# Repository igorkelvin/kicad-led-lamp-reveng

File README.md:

# LED Lamp Rev. Engineering

## Description

Made on KiCad using manual measurements without consulting official schematics for study purposes.

You may find the pdf version of the  in *./extra* folder.

Used a *Pelicano LED* from LLUM for reference, you can check it [at this catalog][catalog].

[catalog]: http://www.bronzearte.com.br/marketing/catalogo.pdf#page=59

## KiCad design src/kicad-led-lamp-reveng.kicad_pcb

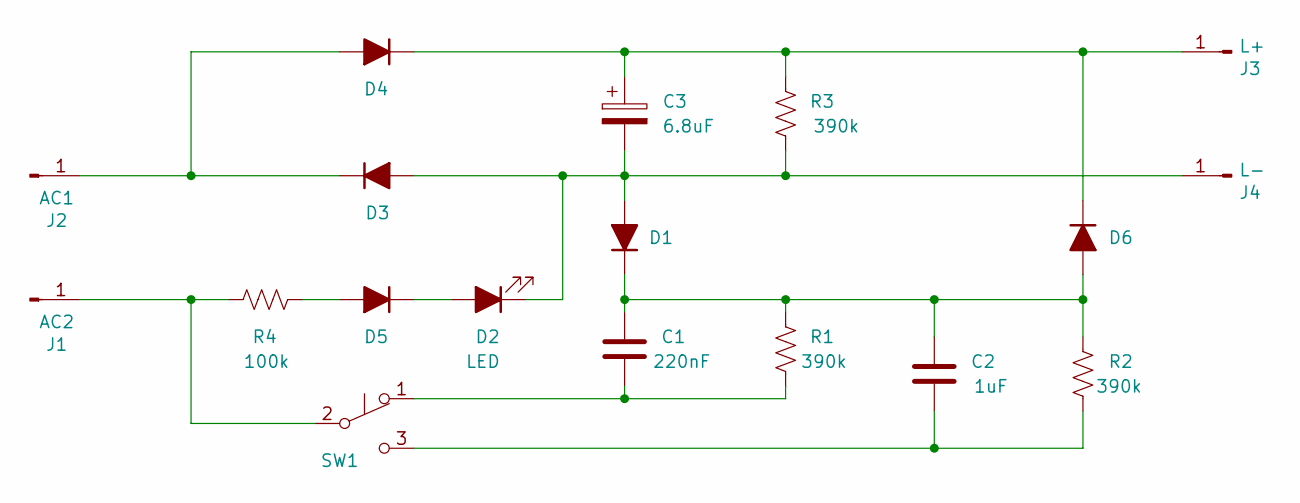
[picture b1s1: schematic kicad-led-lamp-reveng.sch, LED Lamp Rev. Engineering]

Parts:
C1: 220nF; C_Polyester_11.20mm_4.9mm
C2: 1uF; C_Polyester_21.80mm_7.10mm
C3: 6.8uF; CP_Radial_D8.0mm_P5.00mm
D1, D3, D4, D5, D6: 1N4007; DIODE_Axial_DIN0207_L6.3mm_D2.5mm_P7.62mm_Horizontal
D2: LED; LED_D3.0mm
J1: AC2; PinHeader_1x01_P2.54mm_Vertical
J2: AC1; PinHeader_1x01_P2.54mm_Vertical
J3: L+; PinHeader_1x01_P2.54mm_Vertical
J4: L-; PinHeader_1x01_P2.54mm_Vertical
R1, R2, R3: 390k; R_Axial_DIN0207_L6.3mm_D2.5mm_P7.62mm_Horizontal
R4: 100k; R_Axial_DIN0207_L6.3mm_D2.5mm_P7.62mm_Horizontal
SW1: SW_Push_SPDT; Switch_4-Way

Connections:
unnamed: C1.1, R1.1, SW1.1 (A)
unnamed: C1.2, C2.2, D1.1 (K), D6.2 (A), R1.2, R2.1
unnamed: C2.1, R2.2, SW1.3 (C)
unnamed: C3.1, D4.1 (K), D6.1 (K), J3.1, R3.2
unnamed: C3.2, D1.2 (A), D2.1 (K), D3.2 (A), J4.1, R3.1
unnamed: D2.2 (A), D5.1 (K)
unnamed: D3.1 (K), D4.2 (A), J2.1
unnamed: D5.2 (A), R4.2
unnamed: J1.1, R4.1, SW1.2 (B)

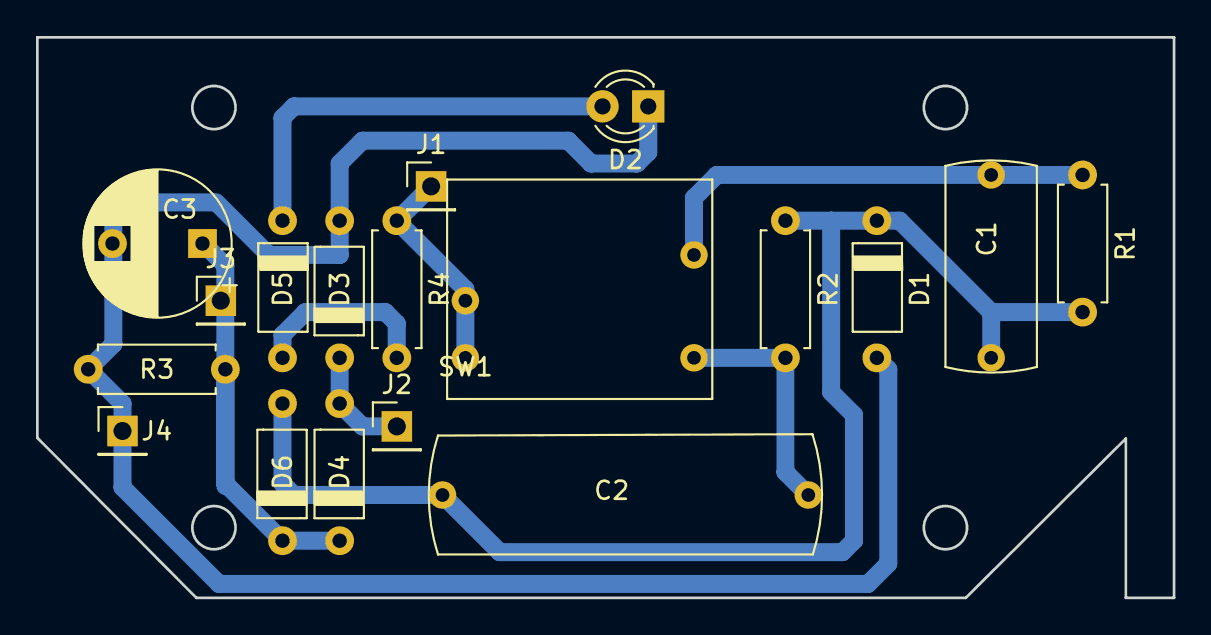
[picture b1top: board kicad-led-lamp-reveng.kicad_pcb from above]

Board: 2 copper layers, 63.2 x 31.1 mm, 18 parts (0 on the bottom side), 9 nets.

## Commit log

2020-08-04 Eeschema components
2020-08-04 eeschema wiring
2020-08-04 Board outline
2020-08-04 Finished pcb layout
2020-08-04 extra
2020-08-07 Schematics rearrangement, changed C3 polarity and Rev1 for pcb & sch
2020-08-07 Corrected D3 and PCB filled zones
2020-08-07 Rev 1 - small changes
2020-08-07 updated 3d solder mask color to green
